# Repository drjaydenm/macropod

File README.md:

# macropod

A basic macro keyboard built from the ground up

## Configuring Macros

To setup your own macro bindings, create a file `key_mappings.h` in the `code/src` directory with the below format. This file will be automatically detected and included in the build.

When editing, be sure to do a clean build to ensure headers are re-included.

```c
#ifndef __KEY_MAPPINGS_H
#define __KEY_MAPPINGS_H

// This will generate a unique GUID following the V4 spec
#define MACRO_KEY_0  GenerateGuid(MacroContext);WriteString(MacroContext, "\e")

// These output the given string
#define MACRO_KEY_1  WriteString(MacroContext, "Macro 1\n")
#define MACRO_KEY_2  GenerateGuid(MacroContext);WriteString(MacroContext, "\e\nMacro 2");
#define MACRO_KEY_3  WriteString(MacroContext, "\t\tMacro 3")
// And so on for the rest of the keys...

#endif
```

## Setup

### Install the GNU Toolchain for ARM Embedded Processors

The toolchain is required to compile for the STM32 target platform

#### MacOS

```bash
brew tap osx-cross/arm

brew install arm-gcc-bin
```

If you are using ST-Link

```bash
brew install stlink
```

If using J-Link, you also need to install the J-Link tools. You can download them from Segger here https://www.segger.com/downloads/jlink/#J-LinkSoftwareAndDocumentationPack

## Building

Run the build

```bash
make
```

Flash to device using ST-Link

```bash
make flash-stlink
```

or using J-Link

```bash
make flash-jlink
```

Inspect memory layout of image

```bash
arm-none-eabi-nm main.elf
```

## Debugging with GDB

### ST-Link GDB Server

```bash
st-util
```

### J-Link GDB Server

```bash
JLinkGDBServer -if swd -device STM32F042K6 -port 4242
```

### GDB

```bash
cd ./code

arm-none-eabi-gdb main.elf

target extended-remote :4242

load

continue

Ctrl^C

info registers

stepi

info registers

quit
```

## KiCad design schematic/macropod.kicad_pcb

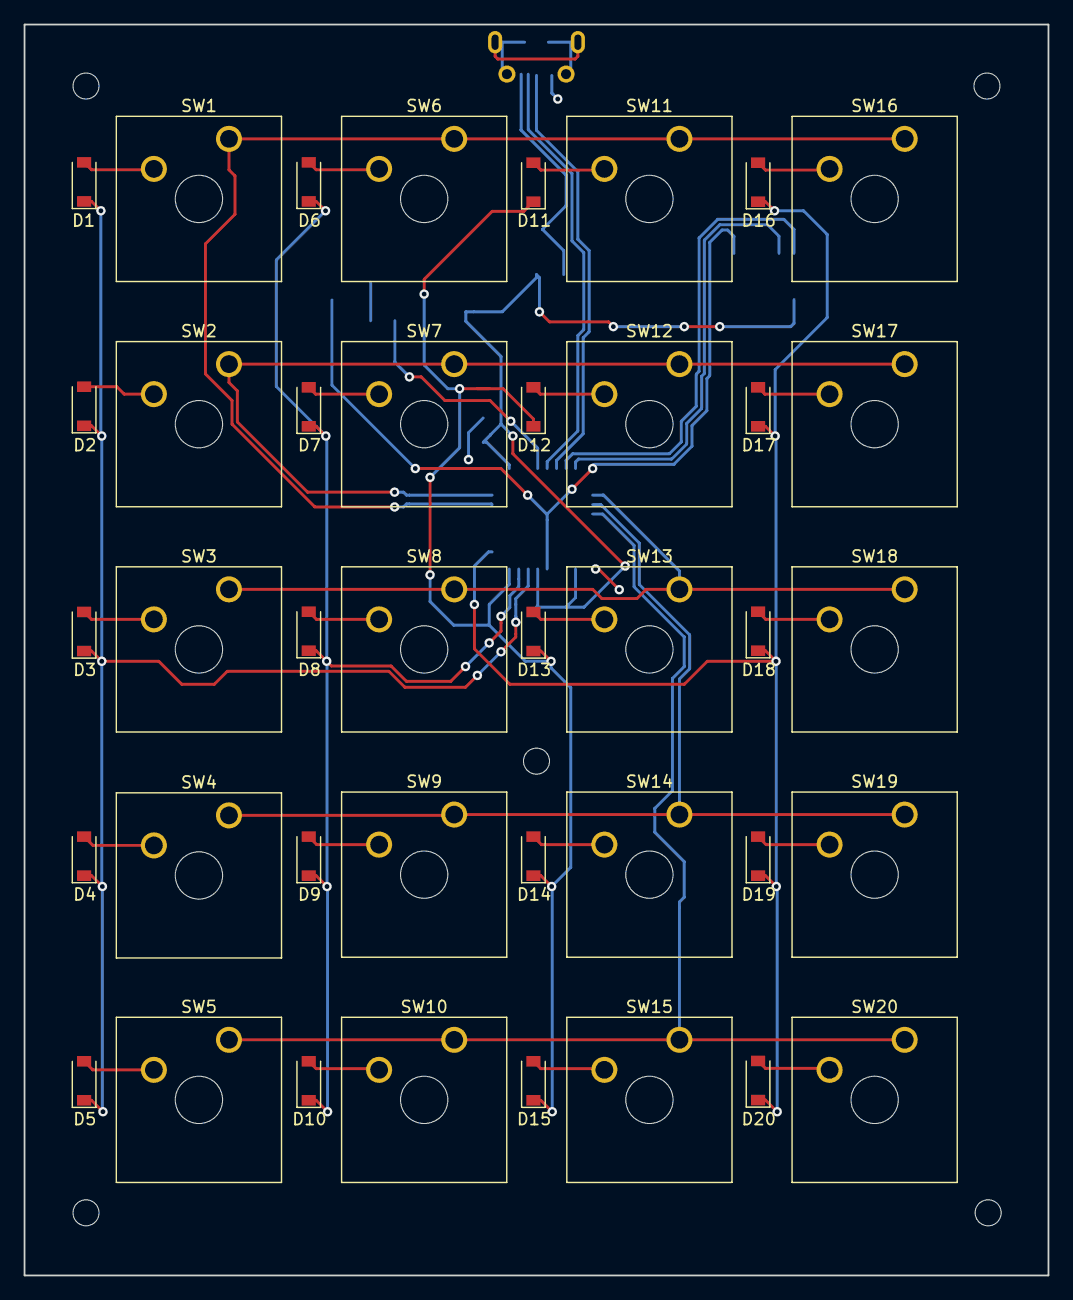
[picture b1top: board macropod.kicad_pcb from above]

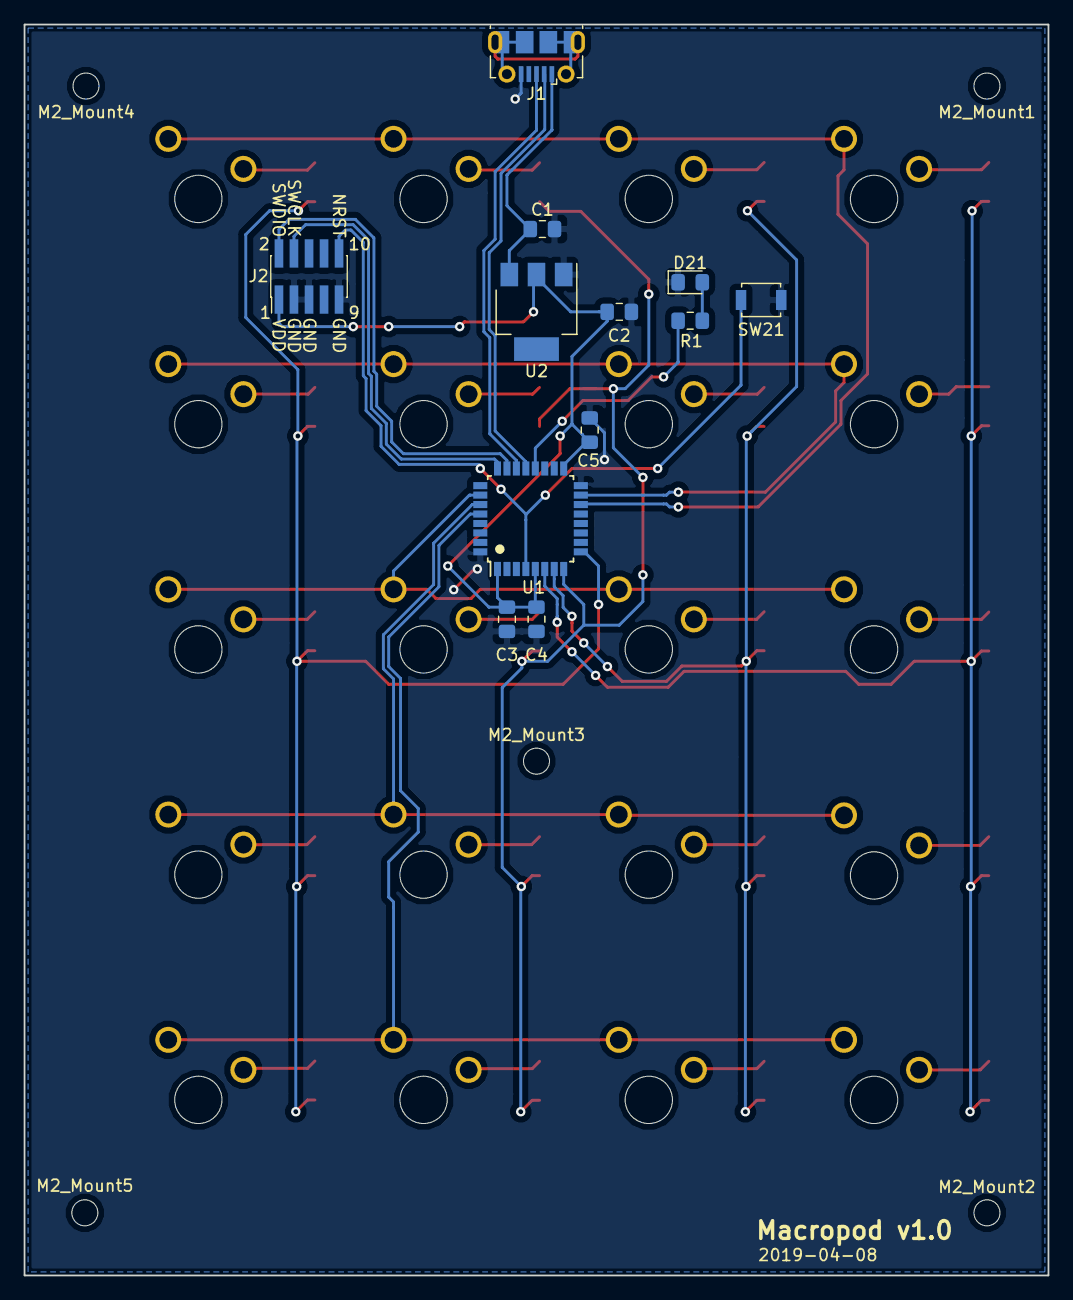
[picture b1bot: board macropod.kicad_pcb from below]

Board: 2 copper layers, 86.6 x 105.8 mm, 57 parts (17 on the bottom side), 39 nets.

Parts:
C1, C2: 4.7uF; C_0805_2012Metric_Pad1.15x1.40mm_HandSolder
C3, C4, C5: 100nF; C_0805_2012Metric_Pad1.15x1.40mm_HandSolder
D1, D2, D3, D4, D5, D6, D7, D8, D9, D10, D11, D12, D13, D14, D15, D16, D17, D18, D19, D20: D; D_SOD-123
D21: LED; LED_0805_2012Metric_Pad1.15x1.40mm_HandSolder
J1: USB_B_Micro; USB_Micro-B_Molex-105017-0001
J2: Conn_ARM_JTAG_SWD_10; PinHeader_2x05_P1.27mm_Vertical_SMD
M2_Mount1, M2_Mount2, M2_Mount3, M2_Mount4, M2_Mount5: MountingHole_2.2mm_M2
R1: 470; R_0805_2012Metric_Pad1.15x1.40mm_HandSolder
SW1, SW2, SW3, SW4, SW5, SW6, SW7, SW8, SW9, SW10, SW11, SW12, SW13, SW14, SW15, SW16, SW17, SW18, SW19, SW20: SW_MK; SW_Cherry_MX1A_1.00u_Plate
SW21: SW_SPST; SW_SPST_B3U-1000P
U1: STM32F042K6Tx; LQFP-32_7x7mm_P0.8mm
U2: LM1117-3.3; SOT-223

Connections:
/COL0: D1.1, D2.1, D3.1, D4.1, D5.1, U1.6
/COL1: D6.1, D7.1, D8.1, D9.1, D10.1, U1.7
/COL2: D11.1, D12.1, D13.1, D14.1, D15.1, U1.8
/COL3: D16.1, D17.1, D18.1, D19.1, D20.1, U1.9
/NRST: J2.10, SW21.2, U1.4
/PWR_LED: R1.1, U1.20
/ROW0: SW1.1, SW6.1, SW11.1, SW16.1, U1.14
/ROW1: SW2.1, SW7.1, SW12.1, SW17.1, U1.15
/ROW2: SW3.1, SW8.1, SW13.1, SW18.1, U1.26
/ROW3: SW4.1, SW9.1, SW14.1, SW19.1, U1.27
/ROW4: SW5.1, SW10.1, SW15.1, SW20.1, U1.28
/SWCLK: J2.4, U1.24
/SWDIO: J2.2, U1.23
/USBD+: J1.3, U1.22
/USBD-: J1.2, U1.21
/VBUS: C1.1, J1.1, U2.3
/VDD: C2.1, C3.1, C4.1, C5.1, J2.1, U1.1, U1.5, U1.17, U2.2
GND: C1.2, C2.2, C3.2, C4.2, C5.2, D21.1, J1.5, J2.3, J2.5, J2.9, SW21.1, U1.16, U1.32, U2.1
unnamed: D1.2, SW1.2
unnamed: D2.2, SW2.2
unnamed: D3.2, SW3.2
unnamed: D4.2, SW4.2
unnamed: D5.2, SW5.2
unnamed: D6.2, SW6.2
unnamed: D7.2, SW7.2
unnamed: D8.2, SW8.2
unnamed: D9.2, SW9.2
unnamed: D10.2, SW10.2
unnamed: D11.2, SW11.2
unnamed: D12.2, SW12.2
unnamed: D13.2, SW13.2
unnamed: D14.2, SW14.2
unnamed: D15.2, SW15.2
unnamed: D16.2, SW16.2
unnamed: D17.2, SW17.2
unnamed: D18.2, SW18.2
unnamed: D19.2, SW19.2
unnamed: D20.2, SW20.2
unnamed: D21.2, R1.2

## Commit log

2019-03-30 Initial commit of the keypad code
2019-04-04 Added macropod schematics
2019-04-04 Added the bill of materials
2019-04-05 Added switch and bumper feet to BOM
2019-04-08 Updated footprints to match BOM components. Applied DRC settings for fabrication
2019-04-18 Updated readme with J-Link GDB debugging instructions
2019-04-19 Added commands for flashing using JLink in makefile
2019-04-25 Updated the makefile to use the elf instead of the bin
2019-04-25 Updated keyboard to use a matrix instead of a key per pin. Started GPIO clocks before configuring pins
2019-04-25 Updated with links to J-Link tools and flash commands
2019-04-25 Set the product names and IDs
2019-04-25 Added an optional header file to declare key mappings to macros. Fixed upper case letters and handled the shift key
2019-04-28 Added support for concat-ing macros together. Added support for all special characters
2019-04-28 Updated readme with multiple macro changes
2019-04-28 Changed readme macros to more realistic examples
2019-06-27 Changed flash to have longer delay, changed GUID to lowercase
